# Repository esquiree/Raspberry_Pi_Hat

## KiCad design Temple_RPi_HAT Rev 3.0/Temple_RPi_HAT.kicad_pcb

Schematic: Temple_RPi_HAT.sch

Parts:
C1: 0.1uF; C_0603
D1: LED; LED_0805
IR1: TSOP36238TR; MPN TSOP36238TR; LCSC C84617
J1, J2: Conn_01x04; Pin_Header_Straight_1x04_Pitch2.54mm
LCD1: I2C_LCD; SSD1306_NO_BOTTOM_SILK_NO_MOUNT
MK1: Housing; BeagleBoneBlue_Extended_2cm
R1, R2, R3, R8: 1K; R_0603
U1: LSM6DS33TR
rpi_Header1: Raspberry_Pi_2_3; RaspberryPi_No Holes

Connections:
+3V3: C1.1, D1.2, IR1.3, J2.1, LCD1.1, R1.2, R2.2, R8.1, U1.1, U1.16; also elsewhere on the board
+5V: J1.1, rpi_Header1.2, rpi_Header1.4; also elsewhere on the board
GND: C1.2, IR1.1, IR1.2, J1.4, J2.2, LCD1.2, U1.8, U1.9, U1.10, U1.11, U1.12, U1.13, U1.15, rpi_Header1.6, rpi_Header1.9, rpi_Header1.14, rpi_Header1.20, rpi_Header1.25, rpi_Header1.30, rpi_Header1.34, rpi_Header1.39; also elsewhere on the board
IR: IR1.4, rpi_Header1.26
MOTOR_EN: R8.2, rpi_Header1.32; also elsewhere on the board
unnamed: D1.1, R3.1
PI_3.3V: rpi_Header1.1, rpi_Header1.17
Prog_LED0: rpi_Header1.22; also elsewhere on the board
QEP_1A: rpi_Header1.15; also elsewhere on the board
QEP_1B: rpi_Header1.16; also elsewhere on the board
QEP_2A: rpi_Header1.11; also elsewhere on the board
QEP_2B: rpi_Header1.12; also elsewhere on the board
QEP_3A: rpi_Header1.37; also elsewhere on the board
QEP_3B: rpi_Header1.13; also elsewhere on the board
QEP_4A: rpi_Header1.29; also elsewhere on the board
QEP_4B: rpi_Header1.31; also elsewhere on the board
RX: J1.2, rpi_Header1.8
SCL: J2.3, LCD1.3, R2.1, U1.2, rpi_Header1.5; also elsewhere on the board
SDA: J2.4, LCD1.4, R1.1, R3.2, U1.3, rpi_Header1.3; also elsewhere on the board
TX: J1.3, rpi_Header1.10

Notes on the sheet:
12 MARCH 2020
Raspberry Pi Hat
3.0
Raspberry Pi HaT
IMU
Raspberry Pi Header
TEST POINTS

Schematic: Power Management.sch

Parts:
BH1: BH123A; BAT_BH123A
C2, C3, C8, C9, C12, C27: 1uF; C_0603
C4, C5, C13, C28: 0.1uF; C_0603
C6, C7, C14, C29: 0.01uF; C_0603
C10, C11: 47uF; CP_Elec_5x5.3; voltage 16V; MPN VES470M1CTR-0505; LCSC C134798
D2, D3, D6, D7, D9, D10, D11: LED; LED_0805
D4, D5, D8: D; D_SMA; MPN SS54; LCSC C22452
F1: Polyfuse 3A; R_1812; MPN SMD300L-6V; LCSC Cost QTY 1 0.08
J8: USB_B_Micro; USB_Micro_B_Female_10103594-0001LF
L1, L2: 4.7uH; L_7.3x6.8; MPN FXL0630-4R7-M; LCSC C167220
R4, R35, R37, R38, R39, R40, R41, R42, R43, R46, R47: 1K; R_0603
R29, R34: 1.5K; R_0603
R30, R32, R45: 200K; R_0603
R31: 13.5K; R_0603
R33: 27K; R_0603
R36: 2K; R_0603
R44: 100K; R_0603
SW1: SW_SPST; Single Dip Siwtch
U4, U5: SY7304DBC; DFN-10-1EP_3x3mm_Pitch0.5mm; MPN SY7304DBC; LCSC C178252
U6: BQ24092DGQR; MSOP-10-1EP_3x3mm_Pitch0.5mm; MPN BQ24092DGQR; LCSC C133237
U7: LMV321; SOT-23-5; MPN LMV321B-TR; LCSC C248567
U8: AZ1117-3.3; SOT-223-3_TabPin2; MPN AMS1117-3.3; LCSC C369933

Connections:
+3V3: C27.1, C28.1, C29.1, R46.2, U8.2 (VO); also elsewhere on the board
+5V: C3.1, C5.1, C7.1, C8.1, C11.1, D5.1, L1.1, R32.2, R37.1, R43.2, R44.2, U4.7, U8.3 (VI); also elsewhere on the board
+10V: C2.1, C4.1, C6.1, C10.1, D4.1, R30.2, R42.2; also elsewhere on the board
+BATT: BH1.1, C9.1, C12.1, C13.1, C14.1, D8.1, L2.1, R29.2, R34.2, R38.1, R40.1, R41.1, U5.7, U6.10, U7.1, U7.5
BATTERY_ENABLE: R4.1, R38.2, U5.9, U7.4
CHG: D2.1, U6.8
GND: C2.2, C3.2, C4.2, C5.2, C6.2, C7.2, C8.2, C9.2, C10.2, C11.2, C12.2, C13.2, C14.2, C27.2, C28.2, C29.2, D6.1, D7.1, D8.2, D9.1, D10.1, D11.1, J8.5, R31.1, R33.1, R35.2, R36.2, R39.2, R45.1, SW1.2, U4.11, U5.11, U6.3, U6.11, U7.2, U8.1 (GND); also elsewhere on the board
unnamed: BH1.2, F1.2
unnamed: D2.2, R29.1
unnamed: D3.2, R34.1
unnamed: D4.2, L1.2, U4.4, U4.5
unnamed: D5.2, L2.2, U5.4, U5.5
unnamed: D6.2, R42.1
unnamed: D7.2, R43.1
unnamed: D9.2, R46.1
unnamed: D10.2, R47.1
unnamed: D11.2, R4.2
unnamed: F1.1, SW1.1
unnamed: R30.1, R31.2, U4.2
unnamed: R32.1, R33.2, U5.2
unnamed: R35.1, U6.2
unnamed: R36.1, U6.4
unnamed: R37.2, U4.9
unnamed: R39.1, R41.2, U6.7
unnamed: R40.2, U6.9
unnamed: R44.1, R45.2, U7.3
PG: D3.1, U6.5
Prog_LED0: R47.2; also elsewhere on the board
V_CHARGE: J8.1, U6.1

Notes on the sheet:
CHARGER
+5V TO +10V BOOST
Status LEDs
BATTERY HOLDER SWITCH & FUSE
3.3V LDO OPTION
POWER MANAGEMENT
12 MAR 2020
POWER MANAGEMENT
3.0
High = 500mA Low = ISET Float = 100mA
V_BAT TO +5V BOOST
UNDER VOLTAGE DETECTION

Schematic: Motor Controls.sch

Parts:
C15, C16, C21: 0.01uF; C_0603
C17, C18, C19, C20, C23: 1uF; C_0603
C22: 0.1uF; C_0603
EN1, EN2, EN3, EN4: Conn_01x04; JST_SH_BM04B-SRSS-TB_04x1.00mm_Straight
J3: 3x8_PinHeader; 3X8_PINHEADER
J4, J5, J6, J7: Conn_01x06; Pin_Header_Straight_1x06_Pitch2.54mm
M1, M2, M3, M4: Conn_01x02; 1_5MM ZH JST
R48: 10; R_0603
SW2: SW_SPDT; SW_SPDT_PCM12; MPN PCM12SMTR; LCSC C319020
U9, U10: DRV8833RTYR; WQFN-16-1EP_4x4mm_Pitch0.65mm_ThermalVias; MPN DRV8833RTYR; LCSC C154936

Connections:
+3V3: SW2.1; also elsewhere on the board
+5V: J3.9, SW2.3; also elsewhere on the board
+10V: U9.10, U10.10; also elsewhere on the board
ENC_PWR: C21.1, C22.1, C23.1, EN1.2, EN2.2, EN3.2, EN4.2, J4.4, J5.4, J6.4, J7.4, R48.2
GND: C15.2, C16.2, C17.2, C18.2, C19.2, C20.2, C21.2, C22.2, C23.2, EN1.1, EN2.1, EN3.1, EN4.1, J3.10, J4.3, J5.3, J6.3, J7.3, U9.1, U9.4, U9.11, U9.17, U10.1, U10.4, U10.11, U10.17; also elsewhere on the board
MOTOR1_NEG: U10.13; also elsewhere on the board
MOTOR1_POS: U10.14; also elsewhere on the board
MOTOR2_NEG: U10.8; also elsewhere on the board
MOTOR2_POS: U10.7; also elsewhere on the board
MOTOR3_NEG: U9.13; also elsewhere on the board
MOTOR3_POS: U9.14; also elsewhere on the board
MOTOR4_NEG: U9.8; also elsewhere on the board
MOTOR4_POS: U9.7; also elsewhere on the board
MOTOR_EN: U9.15, U10.15; also elsewhere on the board
MOTOR_OUT_NEG1: J4.2, M1.2, U10.2
MOTOR_OUT_NEG2: J5.2, M2.2, U10.3
MOTOR_OUT_NEG3: J6.2, M3.2, U9.2
MOTOR_OUT_NEG4: J7.2, M4.2, U9.3
MOTOR_OUT_POS1: J4.1, M1.1, U10.16
MOTOR_OUT_POS2: J5.1, M2.1, U10.5
MOTOR_OUT_POS3: J6.1, M3.1, U9.16
MOTOR_OUT_POS4: J7.1, M4.1, U9.5
unnamed: C15.1, U9.12
unnamed: C16.1, U10.12
unnamed: C17.1, C19.1, U9.9
unnamed: C18.1, C20.1, U10.9
unnamed: R48.1, SW2.2
QEP_1A: EN1.3, J4.5; also elsewhere on the board
QEP_1B: EN1.4, J4.6; also elsewhere on the board
QEP_2A: EN2.3, J5.5; also elsewhere on the board
QEP_2B: EN2.4, J5.6; also elsewhere on the board
QEP_3A: EN3.3, J6.5; also elsewhere on the board
QEP_3B: EN3.4, J6.6; also elsewhere on the board
QEP_4A: EN4.3, J7.5; also elsewhere on the board
QEP_4B: EN4.4, J7.6; also elsewhere on the board
SERVO_1: J3.1; also elsewhere on the board
SERVO_2: J3.2; also elsewhere on the board
SERVO_3: J3.3; also elsewhere on the board
SERVO_4: J3.4; also elsewhere on the board
SERVO_5: J3.5; also elsewhere on the board
SERVO_6: J3.6; also elsewhere on the board
SERVO_7: J3.7; also elsewhere on the board
SERVO_8: J3.8; also elsewhere on the board

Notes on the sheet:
H-Bridge
MOTORS & ENCODERS
SERVOS
MOTOR AND ENCODER IO
MOTOR CONTROLS
12 MARCH 2020
3.0

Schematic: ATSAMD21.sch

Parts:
C24: 0.01uF; C_0603
C25: 0.1uF; C_0603
C26: 1uF; C_0603
J9: Conn_ARM_JTAG_SWD_10; Pin_Header_Straight_2x05_Pitch1.27mm
R5: 1K; R_0603
U2: ATSAMD21E15L; QFN-32-1EP_5x5mm_Pitch0.5mm

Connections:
+3V3: C24.1, C25.1, C26.1, J9.1, R5.1, U2.9, U2.27, U2.28; also elsewhere on the board
ARM_RST: J9.10, R5.2, U2.25
GND: C24.2, C25.2, C26.2, J9.3, J9.5, J9.9, U2.10, U2.26, U2.33; also elsewhere on the board
MOTOR1_NEG: U2.6; also elsewhere on the board
MOTOR1_POS: U2.5; also elsewhere on the board
MOTOR2_NEG: U2.8; also elsewhere on the board
MOTOR2_POS: U2.7; also elsewhere on the board
MOTOR3_NEG: U2.12; also elsewhere on the board
MOTOR3_POS: U2.11; also elsewhere on the board
MOTOR4_NEG: U2.14; also elsewhere on the board
MOTOR4_POS: U2.13; also elsewhere on the board
QEP_1A: U2.1; also elsewhere on the board
QEP_1B: U2.2; also elsewhere on the board
QEP_2A: U2.3; also elsewhere on the board
QEP_2B: U2.4; also elsewhere on the board
QEP_3A: U2.15; also elsewhere on the board
QEP_3B: U2.16; also elsewhere on the board
QEP_4A: U2.31; also elsewhere on the board
QEP_4B: U2.32; also elsewhere on the board
SCL: U2.22; also elsewhere on the board
SDA: U2.21; also elsewhere on the board
SERVO_1: U2.17; also elsewhere on the board
SERVO_2: U2.18; also elsewhere on the board
SERVO_3: U2.19; also elsewhere on the board
SERVO_4: U2.20; also elsewhere on the board
SERVO_5: U2.23; also elsewhere on the board
SERVO_6: U2.24; also elsewhere on the board
SERVO_7: J9.4, U2.29; also elsewhere on the board
SERVO_8: J9.2, U2.30; also elsewhere on the board

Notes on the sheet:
CORTEX ARM M0+
12 MARCH 2020
MICRO CONTROLLER
3.0
ATSAMD21

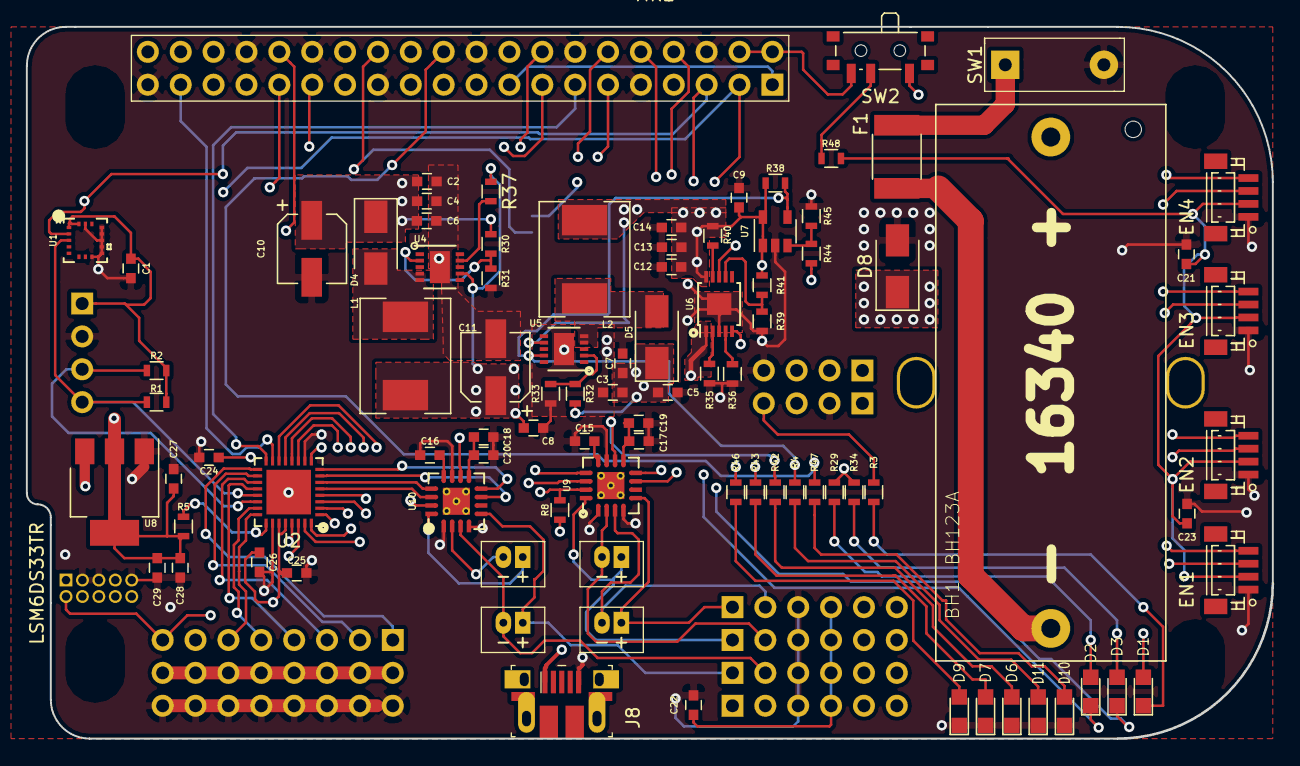
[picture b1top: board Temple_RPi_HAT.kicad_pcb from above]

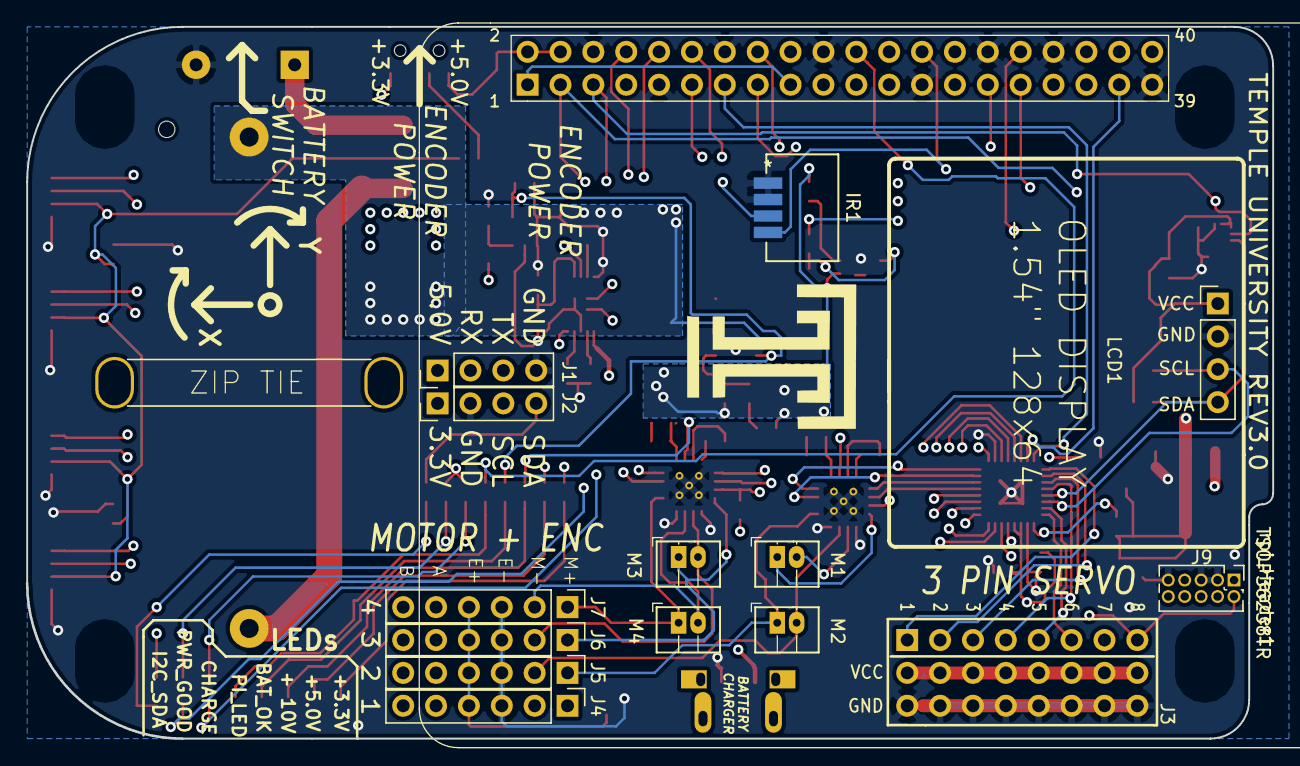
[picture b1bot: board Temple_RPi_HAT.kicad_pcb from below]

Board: 4 copper layers, 96.3 x 55.0 mm, 102 parts (15 on the bottom side), 76 nets.

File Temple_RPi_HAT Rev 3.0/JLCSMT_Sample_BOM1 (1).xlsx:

Comment | Designator | Footprint | LCSC Part #（optional）
0.01uF | C6 C7 C14 C15 C16 C21 C24 C29 | C_0603 | C57112
0.1uF | C1 C4 C5 C13 C22 C25 C28 | C_0603 | C14663
1uF | C2 C3 C8 C9 C12 C17 C18 C19 C20 C23 C26 C27 | C_0603 | C15849
47uF | C10 C11 | CP_Elec_5x5.3 | C134798
D | D4 D5 D8 | D_SMA | C22452
LED | D1 D2 D3 D6 D7 D9 D10 D11 | LED_0805 | C2297
Polyfuse | F1 | R_1812 | C70144
1.5K | R29 R34 | R_0603 | C21190
10 | R48 | R_0603 | C22773
100K | R44 | R_0603 | C23266
13.5K | R31 | R_0603 | C25952
1K | R1 R2 R3 R4 R5 R8 R35 R37 R38 R39 R40 R41 R42 R43 R46 R47 | R_0603 | C21190
200K | R30 R32 R45 | R_0603 | C8218
27K | R33 | R_0603 | C22967
2K | R36 | R_0603 | C22975
AZ1117-3.3 | U8 | SOT-223-3_TabPin2 | C369933
BQ24092DGQR | U6 | MSOP-10-1EP_3x3mm_Pitch0.5mm | C133237
DRV8833RTYR | U9 U10 | WQFN-16-1EP_4x4mm_Pitch0.65mm_ThermalVias | C154936
LMV321 | U7 | SOT-23-5 | C7972
LSM6DS3 | U1 | Bosch_LGA-16 | C95231
SY7304DBC | U4 U5 | DFN-10-1EP_3x3mm_Pitch0.5mm | C178252

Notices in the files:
parts and their libraries:
Copyright 2016 Accelerated Designs. All rights reserved.
